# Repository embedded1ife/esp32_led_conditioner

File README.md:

# Overview
This is one of those projects where it was a "problem" that I created. I decided that, after years of risking my life putting up Christmas lights, I was done. No, not done with Christmas lights, just the cycle. After taking inspiration from [The Hook Up](https://www.youtube.com/channel/UC2gyzKcHbYfqoXA5xbyGXtQ), and [DrZzs](https://www.youtube.com/c/DrZzs), I decided to install LED strips in a way that when they are off, you couldn't tell they were there. Where I deviated from those two installs was the need to wire each strip back to a central point. I wanted a decentralized solution that only required each strip have access to 120V, and the control would come via WiFi.

<image src="images/close_up_gutter.jpg" width="40%">&nbsp;&nbsp;&nbsp;&nbsp;
<image src="images/wall_mounted.jpg" width="40%">

# Details

Starting with the end goal: a device that is compatible with [WLED](https://kno.wled.ge/), has integrated WiFi (required for my decentralized configuration), and is small enough to fit inside a IP68(weatherproof) box for those lawn ornaments. I landed on the ESP32 in a NodeMCU configuration. From there the only thing that was lacking was a way to interface the ESP32 to the LED strips/strings. To solve this problem I designed a board using [KiCAD](https://www.kicad.org/).

## Requirements for board:
- Interface with an ESP32 \([Amazon](https://www.amazon.com/gp/product/B086MJGFVV), [AliExpress](https://www.aliexpress.com/item/1005001757645011.html)\)
- Provide connection for bare wire, or barrel jack (for interior use such as kitchen cabinets), from supply
- Provide connection for bare wire to LED strips
- Provide some voltage and current protection
- Support both 5V and 12V LEDs
- For teh 12V LEDs step down input voltage to a level that the LDO on the ESP32 NodeMCU can tolerate (5V)
  - The voltage regulator has the ability to run at 100% duty cycle making the board 5V and 12V compatible
- Step up the data line to the LEDs from 3.3V to 5V
- All fit inside a [IP68 Box](https://www.amazon.com/gp/product/B07TGHYQF4)

# Materials

<image src="images/pcb_assembled.jpg" width="40%">&nbsp;&nbsp;&nbsp;&nbsp;

## Board
- [PCB](https://oshpark.com/shared_projects/z9dy7YqV)
- [Components](bom.csv) from [Digikey](https://www.digikey.com/)

## ESP32
- [Amazon](https://www.amazon.com/gp/product/B086MJGFVV) or
- [AliExpress](https://www.aliexpress.com/item/1005001757645011.html)

## LED Strips
- [IP65 WS2815 12V](https://www.amazon.com/BTF-LIGHTING-Upgraded-Individually-Addressable-Non-Waterproof/dp/B07LG6KQ55)
  - I picked the WS2815 due to it being a 12V strip and thus reducing the need for power injection

## Hardware
- [IP68 Box](https://www.amazon.com/gp/product/B07TGHYQF4)
- [V-Shaped Channel](https://www.amazon.com/gp/product/B07F6FKGPH) for under the gutters
- [Low Profile Channel](https://www.amazon.com/gp/product/B07KDSYLGG) for the flat surface around the garage

## Supply
- [60W IP67](https://www.amazon.com/gp/product/B07MZP9247)
  - You will want a supply that matches the LEDs voltage because the board just passes the supply voltage on to the LEDs

## ESP32 Firmware

For the firmware I use [WLED](https://kno.wled.ge/). If new to this I recommend starting [here](https://kno.wled.ge/basics/getting-started/).

# Steps
1. Order materials

2. Assemble board

<image src="images/sch.png" width="30%">

3. Plug ESP32 into carrier board and power up

4. [Flash ESP32 with WLED](https://kno.wled.ge/basics/install-binary/)

# Tips
- For the flat aluminum channel around the garage, with about 1/8" of the side of the channel exposed, I wanted it to blend in with the white trim. I ended up using some [self etching primer](https://www.lowes.com/pd/Rust-Oleum-Stops-Rust-Flat-Gray-Spray-Primer-Actual-Net-Contents-12-oz/3728805), and white spray paint.
- After a year of having them up I had a problem where one strip would fade out 50% of the way down the strip, and the other the last 10% of the strip would not turn on. The problem ended up being that I did not protect the cut ends of the led strip and weather had caused them to short out. The image below is of my fix but you can see the chared remains from what happened.

<image src="images/burn_50_90.jpg" width="30%">

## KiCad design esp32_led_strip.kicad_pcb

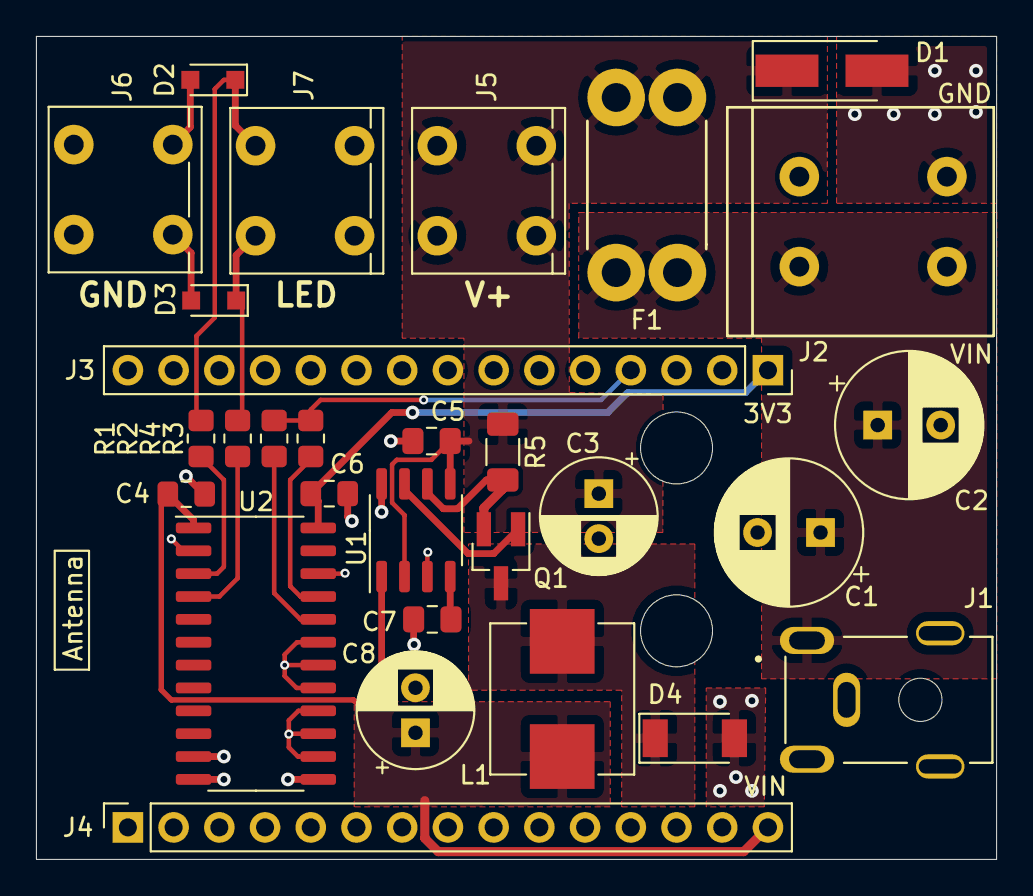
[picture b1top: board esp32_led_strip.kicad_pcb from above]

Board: 2 copper layers, 53.3 x 45.7 mm, 31 parts (0 on the bottom side), 16 nets.

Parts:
C1, C2: 470u; CP_Radial_D8.0mm_P3.50mm
C3, C8: 47u; CP_Radial_D6.3mm_P2.50mm
C4, C6: .1u; C_0805_2012Metric_Pad1.15x1.40mm_HandSolder
C5: .47u; C_0805_2012Metric_Pad1.18x1.45mm_HandSolder
C7: .1u; C_0805_2012Metric_Pad1.18x1.45mm_HandSolder
D1: D_TVS; D_SMA_Handsoldering
D2, D3: D_TVS; D_SOD-323_HandSoldering
D4: ‎PMEG6030EVPX‎; D_SOD-128
F1: Fuse; 3557_mini_fuse
H1, H2: MountingHole; MountingHole_4mm
J1: Barrel_Jack; CUI_PJ-047AH
J2: Screw_Terminal_01x02; 1330180000
J3, J4: Conn_01x15_Female; PinSocket_1x15_P2.54mm_Vertical
J5, J6, J7: Screw_Terminal_01x02; 1825960000
L1: 33uH; ETQ-P5M470YFM
Q1: Q_PMOS_GSD; SOT-23_Handsoldering
R1, R2: 62; R_0805_2012Metric_Pad1.20x1.40mm_HandSolder
R3, R4: 1k; R_0805_2012Metric_Pad1.20x1.40mm_HandSolder
R5: 50m; R_1206_3216Metric_Pad1.30x1.75mm_HandSolder
U1: MAX1626; SO-8_3.9x4.9mm_P1.27mm
U2: 74LVC4245A; SO-24_5.3x15mm_P1.27mm

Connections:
+3V3: C6.1, J3.1, U2.24
+5V: C4.1, C8.1, J4.15, L1.2, U1.1, U2.1
+12V: C3.1, C5.1, D1.1, F1.1, J5.1, J5.2, R5.1, U1.2, U1.5
/LED_CHAN_0: J3.4, R3.1, R4.1
/LED_CHAN_0_5V_A: D2.1, J7.1, R1.2
/LED_CHAN_0_5V_B: D3.1, J7.2, R2.2
GND: C1.2, C2.2, C3.2, C4.2, C5.2, C6.2, C7.2, C8.2, D1.2, D2.2, D3.2, D4.2, J1.2, J2.2, J3.2, J4.14, J6.1, J6.2, U1.3, U1.8, U2.2, U2.11, U2.12, U2.13, U2.14, U2.15, U2.16, U2.17, U2.18, U2.19, U2.22
unnamed: C1.1, C2.1, F1.2, J1.1, J2.1
unnamed: C7.1, U1.4
unnamed: D4.1, L1.1, Q1.3
unnamed: Q1.1, U1.7
unnamed: Q1.2, R5.2, U1.6
unnamed: R1.1, U2.3
unnamed: R2.1, U2.4
unnamed: R3.2, U2.21
unnamed: R4.2, U2.20

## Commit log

2022-03-18 added additional pictures and items
2022-03-30 added additional information to reademe
2022-03-30 included esp32 in materials
2022-04-01 touched up the README
2022-04-04 Create CNAME
2022-07-05 added burn
